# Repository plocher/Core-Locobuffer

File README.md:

# Core-Locobuffer
## License: CERN Open Hardware Licence v1.2

Standalone "locobuffer-style" Loconet interface with I2C expandability

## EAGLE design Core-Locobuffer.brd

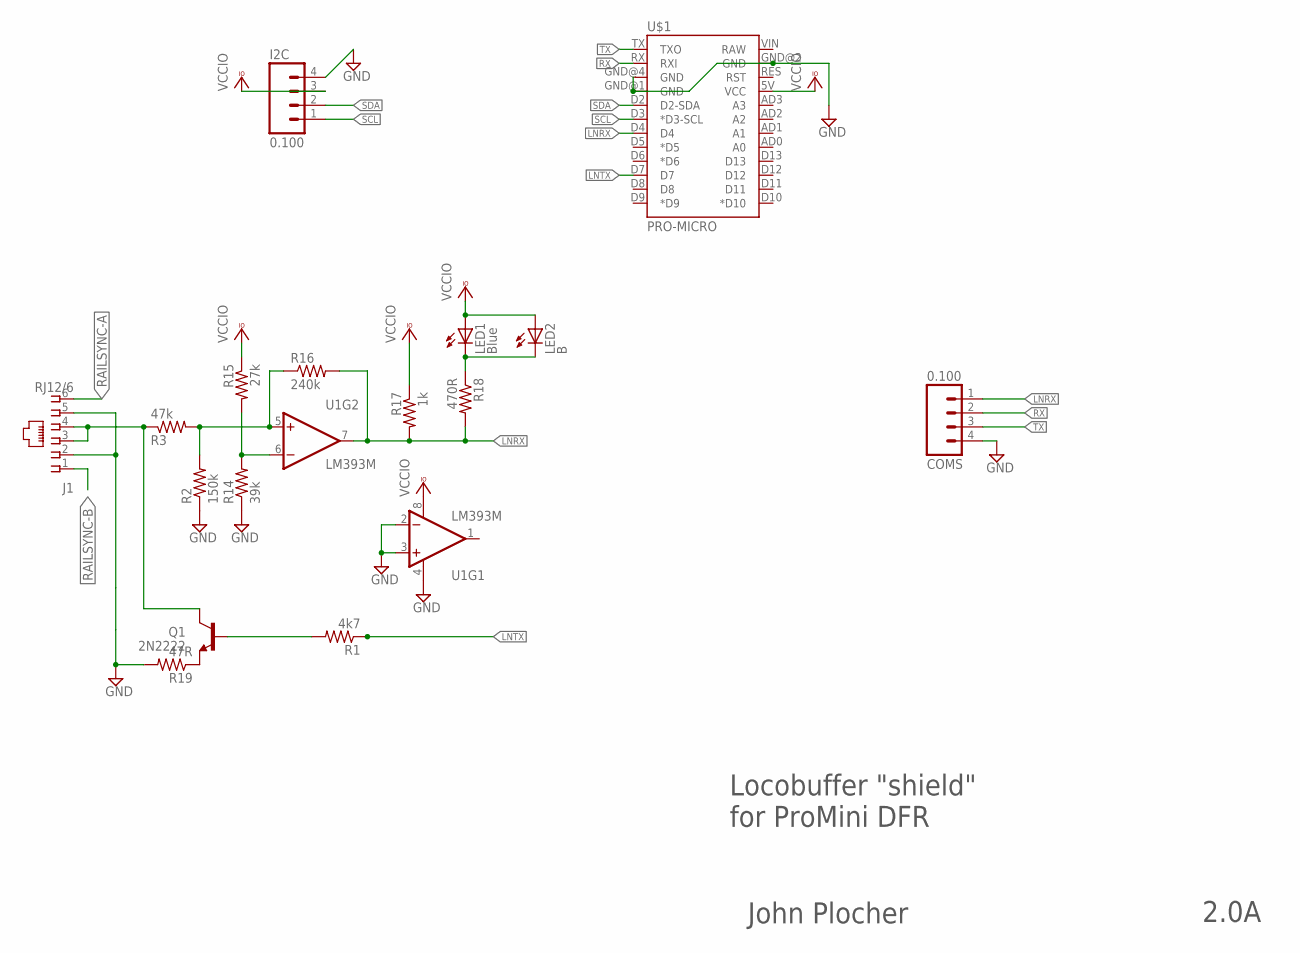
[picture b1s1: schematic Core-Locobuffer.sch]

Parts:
COMS: 0.100; 1X04_LOCK
I2C: 0.100; 1X04_LOCK
J1: RJ12/6; RJ25-PANEL
LED1: Blue; 0603-LED
LED2: B; LED5MM
Q1: 2N2222; SOT23
R1: 4k7; 0603-RES
R2: 150k; 0603-RES
R3: 47k; 0603-RES
R14: 39k; 0603-RES
R15: 27k; 0603-RES
R16: 240k; 0603-RES
R17: 1k; 0603-RES
R18: 470R; 0603-RES
R19: 47R; 0603-RES
U1: LM393M; SO08
U$1: PRO-MICRO; ARDUINO-PRO-MICRO-NOSILK

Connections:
GND: COMS.4, I2C.4, J1.2, J1.5, R2.1, R14.1, R19.2, U1.2 (-IN), U1.3 (+IN), U1.4 (V-), U$1.GND@1 (GND), U$1.GND@2 (GND), U$1.GND@4 (GND)
LNRX: COMS.1, R16.2, R17.2, R18.2, U1.7 (OUT), U$1.D4
LNTX: R1.1, U$1.D7
LOCONET: J1.3, J1.4, Q1.3 (C), R3.1
unnamed: Q1.1 (B), R1.2
unnamed: LED1.C, LED2.K (C), R18.1
unnamed: R2.2, R3.2, R16.1, U1.5 (+IN)
unnamed: R14.2, R15.2, U1.6 (-IN)
unnamed: Q1.2 (E), R19.1
RAILSYNC-A: J1.6
RAILSYNC-B: J1.1
RX: COMS.2, U$1.RX (RXI)
SCL: I2C.1, U$1.D3 (*D3-SCL)
SDA: I2C.2, U$1.D2 (D2-SDA)
TX: COMS.3, U$1.TX (TXO)
VCCIO: I2C.3, LED1.A, LED2.A, R15.1, R17.1, U1.8 (V+), U$1.5V (VCC)

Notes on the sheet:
Locobuffer "shield" for ProMini DFR
John Plocher
2.0A

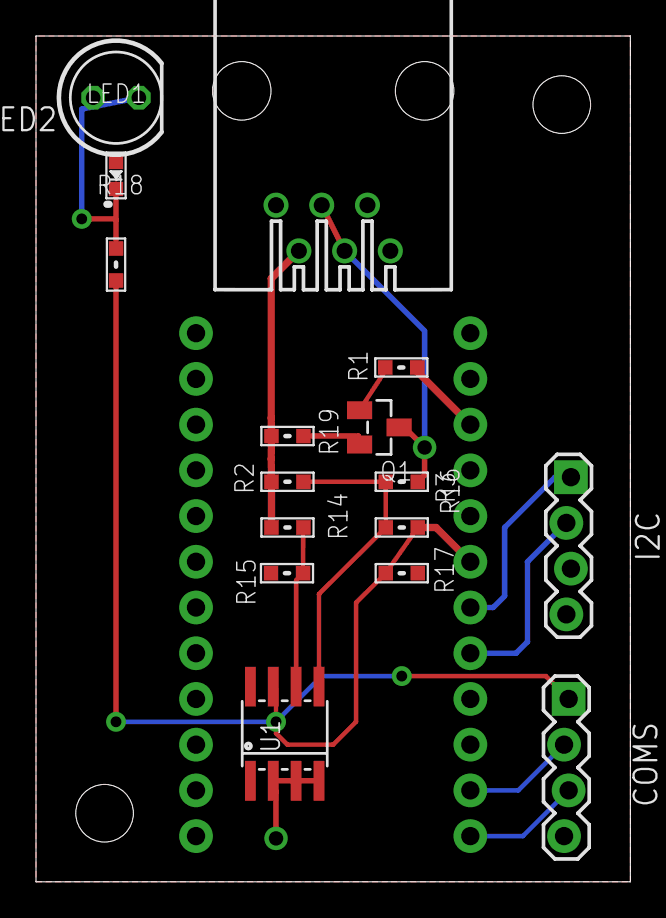
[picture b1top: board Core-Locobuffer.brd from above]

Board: 2 copper layers, 33.0 x 47.0 mm, 17 parts (0 on the bottom side), 14 nets.

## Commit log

2019-12-09 added graphic
2020-05-04 updated tags
2020-10-05 added values for connectors
2020-10-06 normalized values
